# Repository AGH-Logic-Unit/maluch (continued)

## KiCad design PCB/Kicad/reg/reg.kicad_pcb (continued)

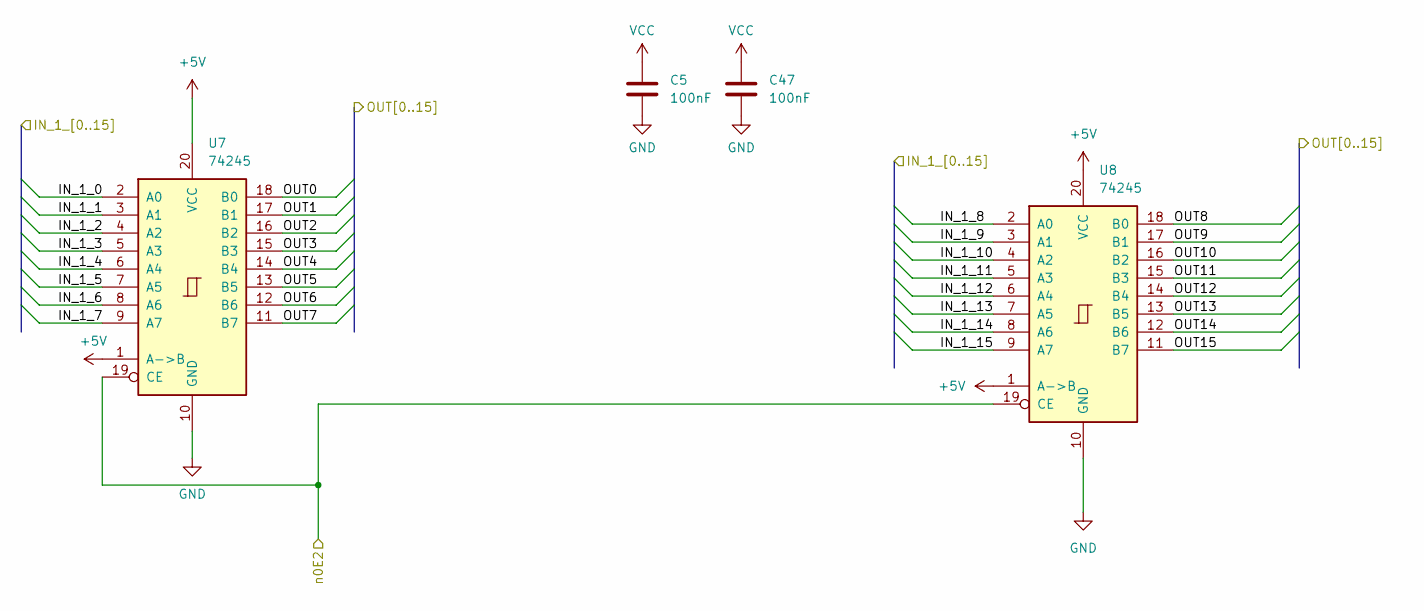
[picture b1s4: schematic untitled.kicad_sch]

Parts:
C5, C47: 100nF; C_0402_1005Metric
U7, U8: 74245; TSSOP-20_4.4x6.5mm_P0.65mm

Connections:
+5V: C5.1, C47.1, U7.1 (A->B), U7.20 (VCC), U8.1 (A->B), U8.20 (VCC); also elsewhere on the board
/16 bit buffor23/OUT0: U7.18 (B0); also elsewhere on the board
/16 bit buffor23/OUT1: U7.17 (B1); also elsewhere on the board
/16 bit buffor23/OUT2: U7.16 (B2); also elsewhere on the board
/16 bit buffor23/OUT3: U7.15 (B3); also elsewhere on the board
/16 bit buffor23/OUT4: U7.14 (B4); also elsewhere on the board
/16 bit buffor23/OUT5: U7.13 (B5); also elsewhere on the board
/16 bit buffor23/OUT6: U7.12 (B6); also elsewhere on the board
/16 bit buffor23/OUT7: U7.11 (B7); also elsewhere on the board
/16 bit buffor23/OUT8: U8.18 (B0); also elsewhere on the board
/16 bit buffor23/OUT9: U8.17 (B1); also elsewhere on the board
/16 bit buffor23/OUT10: U8.16 (B2); also elsewhere on the board
/16 bit buffor23/OUT11: U8.15 (B3); also elsewhere on the board
/16 bit buffor23/OUT12: U8.14 (B4); also elsewhere on the board
/16 bit buffor23/OUT13: U8.13 (B5); also elsewhere on the board
/16 bit buffor23/OUT14: U8.12 (B6); also elsewhere on the board
/16 bit buffor23/OUT15: U8.11 (B7); also elsewhere on the board
/data0: U7.2 (A0); also elsewhere on the board
/data1: U7.3 (A1); also elsewhere on the board
/data2: U7.4 (A2); also elsewhere on the board
/data3: U7.5 (A3); also elsewhere on the board
/data4: U7.6 (A4); also elsewhere on the board
/data5: U7.7 (A5); also elsewhere on the board
/data6: U7.8 (A6); also elsewhere on the board
/data7: U7.9 (A7); also elsewhere on the board
/data8: U8.2 (A0); also elsewhere on the board
/data9: U8.3 (A1); also elsewhere on the board
/data10: U8.4 (A2); also elsewhere on the board
/data11: U8.5 (A3); also elsewhere on the board
/data12: U8.6 (A4); also elsewhere on the board
/data13: U8.7 (A5); also elsewhere on the board
/data14: U8.8 (A6); also elsewhere on the board
/data15: U8.9 (A7); also elsewhere on the board
/r1we: U7.19 (CE), U8.19 (CE); also elsewhere on the board
GND: C5.2, C47.2, U7.10 (GND), U8.10 (GND); also elsewhere on the board

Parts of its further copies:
C6, C11, C12, C48, C49, C50, C51, C52, C53, C54, C55, C56, C57, C58, C59, C60, C61, C62, C63, C64, C65, C66, C67, C68, C69, C70, C71, C72, C73, C74, C75, C76, C77, C78, C79, C80, C81, C82, C83, C84, C87, C88: 100nF; C_0402_1005Metric
U5, U6, U9, U10, U11, U12, U15, U16, U21, U22, U81, U82, U107, U108, U109, U110, U111, U112, U113, U114, U115, U116, U117, U118, U119, U120, U121, U122, U123, U124, U125, U126, U127, U128, U129, U130, U131, U132, U133, U134, U135, U136: 74245; TSSOP-20_4.4x6.5mm_P0.65mm

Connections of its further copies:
+5V: C6.1, C11.1, C12.1, C48.1, C49.1, C50.1, C51.1, C52.1, C53.1, C54.1, C55.1, C56.1, C57.1, C58.1, C59.1, C60.1, C61.1, C62.1, C63.1, C64.1, C65.1, C66.1, C67.1, C68.1, C69.1, C70.1, C71.1, C72.1, C73.1, C74.1, C75.1, C76.1, C77.1, C78.1, C79.1, C80.1, C81.1, C82.1, C83.1, C84.1, C87.1, C88.1, U5.1 (A->B), U5.20 (VCC), U6.1 (A->B), U6.20 (VCC), U9.1 (A->B), U9.20 (VCC), U10.1 (A->B), U10.20 (VCC), U11.1 (A->B), U11.20 (VCC), U12.1 (A->B), U12.20 (VCC), U15.1 (A->B), U15.20 (VCC), U16.1 (A->B), U16.20 (VCC), U21.1 (A->B), U21.20 (VCC), U22.1 (A->B), U22.20 (VCC), U81.1 (A->B), U81.20 (VCC), U82.1 (A->B), U82.20 (VCC), U107.1 (A->B), U107.20 (VCC), U108.1 (A->B), U108.20 (VCC), U109.1 (A->B), U109.20 (VCC), U110.1 (A->B), U110.20 (VCC), U111.1 (A->B), U111.20 (VCC), U112.1 (A->B), U112.20 (VCC), U113.1 (A->B), U113.20 (VCC), U114.1 (A->B), U114.20 (VCC), U115.1 (A->B), U115.20 (VCC), U116.1 (A->B), U116.20 (VCC), U117.1 (A->B), U117.20 (VCC), U118.1 (A->B), U118.20 (VCC), U119.1 (A->B), U119.20 (VCC), U120.1 (A->B), U120.20 (VCC), U121.1 (A->B), U121.20 (VCC), U122.1 (A->B), U122.20 (VCC), U123.1 (A->B), U123.20 (VCC), U124.1 (A->B), U124.20 (VCC), U125.1 (A->B), U125.20 (VCC), U126.1 (A->B), U126.20 (VCC), U127.1 (A->B), U127.20 (VCC), U128.1 (A->B), U128.20 (VCC), U129.1 (A->B), U129.20 (VCC), U130.1 (A->B), U130.20 (VCC), U131.1 (A->B), U131.20 (VCC), U132.1 (A->B), U132.20 (VCC), U133.1 (A->B), U133.20 (VCC), U134.1 (A->B), U134.20 (VCC), U135.1 (A->B), U135.20 (VCC), U136.1 (A->B), U136.20 (VCC); also elsewhere on the board
/16 bit buffor3/n0E2: U5.19 (CE), U6.19 (CE); also elsewhere on the board
/16 bit buffor21/OUT0: U5.18 (B0), U9.18 (B0), U15.2 (A0)
/16 bit buffor21/OUT1: U5.17 (B1), U9.17 (B1), U15.3 (A1)
/16 bit buffor21/OUT2: U5.16 (B2), U9.16 (B2), U15.4 (A2)
/16 bit buffor21/OUT3: U5.15 (B3), U9.15 (B3), U15.5 (A3)
/16 bit buffor21/OUT4: U5.14 (B4), U9.14 (B4), U15.6 (A4)
/16 bit buffor21/OUT5: U5.13 (B5), U9.13 (B5), U15.7 (A5)
/16 bit buffor21/OUT6: U5.12 (B6), U9.12 (B6), U15.8 (A6)
/16 bit buffor21/OUT7: U5.11 (B7), U9.11 (B7), U15.9 (A7)
/16 bit buffor21/OUT8: U6.18 (B0), U10.18 (B0), U16.2 (A0)
/16 bit buffor21/OUT9: U6.17 (B1), U10.17 (B1), U16.3 (A1)
/16 bit buffor21/OUT10: U6.16 (B2), U10.16 (B2), U16.4 (A2)
/16 bit buffor21/OUT11: U6.15 (B3), U10.15 (B3), U16.5 (A3)
/16 bit buffor21/OUT12: U6.14 (B4), U10.14 (B4), U16.6 (A4)
/16 bit buffor21/OUT13: U6.13 (B5), U10.13 (B5), U16.7 (A5)
/16 bit buffor21/OUT14: U6.12 (B6), U10.12 (B6), U16.8 (A6)
/16 bit buffor21/OUT15: U6.11 (B7), U10.11 (B7), U16.9 (A7)
/16 bit buffor23/OUT0: U11.18 (B0); also elsewhere on the board
/16 bit buffor23/OUT1: U11.17 (B1); also elsewhere on the board
/16 bit buffor23/OUT2: U11.16 (B2); also elsewhere on the board
/16 bit buffor23/OUT3: U11.15 (B3); also elsewhere on the board
/16 bit buffor23/OUT4: U11.14 (B4); also elsewhere on the board
/16 bit buffor23/OUT5: U11.13 (B5); also elsewhere on the board
/16 bit buffor23/OUT6: U11.12 (B6); also elsewhere on the board
/16 bit buffor23/OUT7: U11.11 (B7); also elsewhere on the board
/16 bit buffor23/OUT8: U12.18 (B0); also elsewhere on the board
/16 bit buffor23/OUT9: U12.17 (B1); also elsewhere on the board
/16 bit buffor23/OUT10: U12.16 (B2); also elsewhere on the board
/16 bit buffor23/OUT11: U12.15 (B3); also elsewhere on the board
/16 bit buffor23/OUT12: U12.14 (B4); also elsewhere on the board
/16 bit buffor23/OUT13: U12.13 (B5); also elsewhere on the board
/16 bit buffor23/OUT14: U12.12 (B6); also elsewhere on the board
/16 bit buffor23/OUT15: U12.11 (B7); also elsewhere on the board
/16 bit buffor23/n0E2: U11.19 (CE), U12.19 (CE); also elsewhere on the board
/16 bit buffor25/OUT0: U15.18 (B0), U21.18 (B0); also elsewhere on the board
/16 bit buffor25/OUT1: U15.17 (B1), U21.17 (B1); also elsewhere on the board
/16 bit buffor25/OUT2: U15.16 (B2), U21.16 (B2); also elsewhere on the board
/16 bit buffor25/OUT3: U15.15 (B3), U21.15 (B3); also elsewhere on the board
/16 bit buffor25/OUT4: U15.14 (B4), U21.14 (B4); also elsewhere on the board
/16 bit buffor25/OUT5: U15.13 (B5), U21.13 (B5); also elsewhere on the board
/16 bit buffor25/OUT6: U15.12 (B6), U21.12 (B6); also elsewhere on the board
/16 bit buffor25/OUT7: U15.11 (B7), U21.11 (B7); also elsewhere on the board
/16 bit buffor25/OUT8: U16.18 (B0), U22.18 (B0); also elsewhere on the board
/16 bit buffor25/OUT9: U16.17 (B1), U22.17 (B1); also elsewhere on the board
/16 bit buffor25/OUT10: U16.16 (B2), U22.16 (B2); also elsewhere on the board
/16 bit buffor25/OUT11: U16.15 (B3), U22.15 (B3); also elsewhere on the board
/16 bit buffor25/OUT12: U16.14 (B4), U22.14 (B4); also elsewhere on the board
/16 bit buffor25/OUT13: U16.13 (B5), U22.13 (B5); also elsewhere on the board
/16 bit buffor25/OUT14: U16.12 (B6), U22.12 (B6); also elsewhere on the board
/16 bit buffor25/OUT15: U16.11 (B7), U22.11 (B7); also elsewhere on the board
/16 bit buffor26/n0E2: U21.19 (CE), U22.19 (CE); also elsewhere on the board
/16 bit buffor28/IN_1_0: U109.2 (A0); also elsewhere on the board
/16 bit buffor28/IN_1_1: U109.3 (A1); also elsewhere on the board
/16 bit buffor28/IN_1_2: U109.4 (A2); also elsewhere on the board
/16 bit buffor28/IN_1_3: U109.5 (A3); also elsewhere on the board
/16 bit buffor28/IN_1_4: U109.6 (A4); also elsewhere on the board
/16 bit buffor28/IN_1_5: U109.7 (A5); also elsewhere on the board
/16 bit buffor28/IN_1_6: U109.8 (A6); also elsewhere on the board
/16 bit buffor28/IN_1_7: U109.9 (A7); also elsewhere on the board
/16 bit buffor28/IN_1_8: U110.2 (A0); also elsewhere on the board
/16 bit buffor28/IN_1_9: U110.3 (A1); also elsewhere on the board
/16 bit buffor28/IN_1_10: U110.4 (A2); also elsewhere on the board
/16 bit buffor28/IN_1_11: U110.5 (A3); also elsewhere on the board
/16 bit buffor28/IN_1_12: U110.6 (A4); also elsewhere on the board
/16 bit buffor28/IN_1_13: U110.7 (A5); also elsewhere on the board
/16 bit buffor28/IN_1_14: U110.8 (A6); also elsewhere on the board
/16 bit buffor28/IN_1_15: U110.9 (A7); also elsewhere on the board
/16 bit buffor29/IN_1_0: U111.2 (A0); also elsewhere on the board
/16 bit buffor29/IN_1_1: U111.3 (A1); also elsewhere on the board
/16 bit buffor29/IN_1_2: U111.4 (A2); also elsewhere on the board
/16 bit buffor29/IN_1_3: U111.5 (A3); also elsewhere on the board
/16 bit buffor29/IN_1_4: U111.6 (A4); also elsewhere on the board
/16 bit buffor29/IN_1_5: U111.7 (A5); also elsewhere on the board
/16 bit buffor29/IN_1_6: U111.8 (A6); also elsewhere on the board
/16 bit buffor29/IN_1_7: U111.9 (A7); also elsewhere on the board
/16 bit buffor29/IN_1_8: U112.2 (A0); also elsewhere on the board
/16 bit buffor29/IN_1_9: U112.3 (A1); also elsewhere on the board
/16 bit buffor29/IN_1_10: U112.4 (A2); also elsewhere on the board
/16 bit buffor29/IN_1_11: U112.5 (A3); also elsewhere on the board
/16 bit buffor29/IN_1_12: U112.6 (A4); also elsewhere on the board
/16 bit buffor29/IN_1_13: U112.7 (A5); also elsewhere on the board
/16 bit buffor29/IN_1_14: U112.8 (A6); also elsewhere on the board
/16 bit buffor29/IN_1_15: U112.9 (A7); also elsewhere on the board
/16 bit buffor30/IN_1_0: U113.2 (A0); also elsewhere on the board
/16 bit buffor30/IN_1_1: U113.3 (A1); also elsewhere on the board
/16 bit buffor30/IN_1_2: U113.4 (A2); also elsewhere on the board
/16 bit buffor30/IN_1_3: U113.5 (A3); also elsewhere on the board
/16 bit buffor30/IN_1_4: U113.6 (A4); also elsewhere on the board
/16 bit buffor30/IN_1_5: U113.7 (A5); also elsewhere on the board
/16 bit buffor30/IN_1_6: U113.8 (A6); also elsewhere on the board
/16 bit buffor30/IN_1_7: U113.9 (A7); also elsewhere on the board
/16 bit buffor30/IN_1_8: U114.2 (A0); also elsewhere on the board
/16 bit buffor30/IN_1_9: U114.3 (A1); also elsewhere on the board
/16 bit buffor30/IN_1_10: U114.4 (A2); also elsewhere on the board
/16 bit buffor30/IN_1_11: U114.5 (A3); also elsewhere on the board
/16 bit buffor30/IN_1_12: U114.6 (A4); also elsewhere on the board
/16 bit buffor30/IN_1_13: U114.7 (A5); also elsewhere on the board
/16 bit buffor30/IN_1_14: U114.8 (A6); also elsewhere on the board
/16 bit buffor30/IN_1_15: U114.9 (A7); also elsewhere on the board
/16 bit buffor31/IN_1_0: U115.2 (A0); also elsewhere on the board
/16 bit buffor31/IN_1_1: U115.3 (A1); also elsewhere on the board
/16 bit buffor31/IN_1_2: U115.4 (A2); also elsewhere on the board
/16 bit buffor31/IN_1_3: U115.5 (A3); also elsewhere on the board
/16 bit buffor31/IN_1_4: U115.6 (A4); also elsewhere on the board
/16 bit buffor31/IN_1_5: U115.7 (A5); also elsewhere on the board
/16 bit buffor31/IN_1_6: U115.8 (A6); also elsewhere on the board
/16 bit buffor31/IN_1_7: U115.9 (A7); also elsewhere on the board
/16 bit buffor31/IN_1_8: U116.2 (A0); also elsewhere on the board
/16 bit buffor31/IN_1_9: U116.3 (A1); also elsewhere on the board
/16 bit buffor31/IN_1_10: U116.4 (A2); also elsewhere on the board
/16 bit buffor31/IN_1_11: U116.5 (A3); also elsewhere on the board
/16 bit buffor31/IN_1_12: U116.6 (A4); also elsewhere on the board
/16 bit buffor31/IN_1_13: U116.7 (A5); also elsewhere on the board
/16 bit buffor31/IN_1_14: U116.8 (A6); also elsewhere on the board
/16 bit buffor31/IN_1_15: U116.9 (A7); also elsewhere on the board
/16 bit buffor32/IN_1_0: U117.2 (A0); also elsewhere on the board
/16 bit buffor32/IN_1_1: U117.3 (A1); also elsewhere on the board
/16 bit buffor32/IN_1_2: U117.4 (A2); also elsewhere on the board
/16 bit buffor32/IN_1_3: U117.5 (A3); also elsewhere on the board
/16 bit buffor32/IN_1_4: U117.6 (A4); also elsewhere on the board
/16 bit buffor32/IN_1_5: U117.7 (A5); also elsewhere on the board
/16 bit buffor32/IN_1_6: U117.8 (A6); also elsewhere on the board
/16 bit buffor32/IN_1_7: U117.9 (A7); also elsewhere on the board
/16 bit buffor32/IN_1_8: U118.2 (A0); also elsewhere on the board
/16 bit buffor32/IN_1_9: U118.3 (A1); also elsewhere on the board
/16 bit buffor32/IN_1_10: U118.4 (A2); also elsewhere on the board
/16 bit buffor32/IN_1_11: U118.5 (A3); also elsewhere on the board
/16 bit buffor32/IN_1_12: U118.6 (A4); also elsewhere on the board
/16 bit buffor32/IN_1_13: U118.7 (A5); also elsewhere on the board
/16 bit buffor32/IN_1_14: U118.8 (A6); also elsewhere on the board
/16 bit buffor32/IN_1_15: U118.9 (A7); also elsewhere on the board
/16 bit buffor33/IN_1_0: U119.2 (A0); also elsewhere on the board
/16 bit buffor33/IN_1_1: U119.3 (A1); also elsewhere on the board
/16 bit buffor33/IN_1_2: U119.4 (A2); also elsewhere on the board
/16 bit buffor33/IN_1_3: U119.5 (A3); also elsewhere on the board
/16 bit buffor33/IN_1_4: U119.6 (A4); also elsewhere on the board
/16 bit buffor33/IN_1_5: U119.7 (A5); also elsewhere on the board
/16 bit buffor33/IN_1_6: U119.8 (A6); also elsewhere on the board
/16 bit buffor33/IN_1_7: U119.9 (A7); also elsewhere on the board
/16 bit buffor33/IN_1_8: U120.2 (A0); also elsewhere on the board
/16 bit buffor33/IN_1_9: U120.3 (A1); also elsewhere on the board
/16 bit buffor33/IN_1_10: U120.4 (A2); also elsewhere on the board
/16 bit buffor33/IN_1_11: U120.5 (A3); also elsewhere on the board
/16 bit buffor33/IN_1_12: U120.6 (A4); also elsewhere on the board
/16 bit buffor33/IN_1_13: U120.7 (A5); also elsewhere on the board
/16 bit buffor33/IN_1_14: U120.8 (A6); also elsewhere on the board
/16 bit buffor33/IN_1_15: U120.9 (A7); also elsewhere on the board
/16 bit buffor34/IN_1_0: U121.2 (A0); also elsewhere on the board
/16 bit buffor34/IN_1_1: U121.3 (A1); also elsewhere on the board
/16 bit buffor34/IN_1_2: U121.4 (A2); also elsewhere on the board
/16 bit buffor34/IN_1_3: U121.5 (A3); also elsewhere on the board
/16 bit buffor34/IN_1_4: U121.6 (A4); also elsewhere on the board
/16 bit buffor34/IN_1_5: U121.7 (A5); also elsewhere on the board
/16 bit buffor34/IN_1_6: U121.8 (A6); also elsewhere on the board
/16 bit buffor34/IN_1_7: U121.9 (A7); also elsewhere on the board
/16 bit buffor34/IN_1_8: U122.2 (A0); also elsewhere on the board
/16 bit buffor34/IN_1_9: U122.3 (A1); also elsewhere on the board
/16 bit buffor34/IN_1_10: U122.4 (A2); also elsewhere on the board
/16 bit buffor34/IN_1_11: U122.5 (A3); also elsewhere on the board
/16 bit buffor34/IN_1_12: U122.6 (A4); also elsewhere on the board
/16 bit buffor34/IN_1_13: U122.7 (A5); also elsewhere on the board
/16 bit buffor34/IN_1_14: U122.8 (A6); also elsewhere on the board
/16 bit buffor34/IN_1_15: U122.9 (A7); also elsewhere on the board
/16 bit buffor35/IN_1_0: U123.2 (A0); also elsewhere on the board
/16 bit buffor35/IN_1_1: U123.3 (A1); also elsewhere on the board
/16 bit buffor35/IN_1_2: U123.4 (A2); also elsewhere on the board
/16 bit buffor35/IN_1_3: U123.5 (A3); also elsewhere on the board
/16 bit buffor35/IN_1_4: U123.6 (A4); also elsewhere on the board
/16 bit buffor35/IN_1_5: U123.7 (A5); also elsewhere on the board
/16 bit buffor35/IN_1_6: U123.8 (A6); also elsewhere on the board
/16 bit buffor35/IN_1_7: U123.9 (A7); also elsewhere on the board
/16 bit buffor35/IN_1_8: U124.2 (A0); also elsewhere on the board
/16 bit buffor35/IN_1_9: U124.3 (A1); also elsewhere on the board
/16 bit buffor35/IN_1_10: U124.4 (A2); also elsewhere on the board
/16 bit buffor35/IN_1_11: U124.5 (A3); also elsewhere on the board
/16 bit buffor35/IN_1_12: U124.6 (A4); also elsewhere on the board
/16 bit buffor35/IN_1_13: U124.7 (A5); also elsewhere on the board
/16 bit buffor35/IN_1_14: U124.8 (A6); also elsewhere on the board
/16 bit buffor35/IN_1_15: U124.9 (A7); also elsewhere on the board
/16 bit buffor36/IN_1_0: U125.2 (A0); also elsewhere on the board
/16 bit buffor36/IN_1_1: U125.3 (A1); also elsewhere on the board
/16 bit buffor36/IN_1_2: U125.4 (A2); also elsewhere on the board
/16 bit buffor36/IN_1_3: U125.5 (A3); also elsewhere on the board
/16 bit buffor36/IN_1_4: U125.6 (A4); also elsewhere on the board
/16 bit buffor36/IN_1_5: U125.7 (A5); also elsewhere on the board
/16 bit buffor36/IN_1_6: U125.8 (A6); also elsewhere on the board
/16 bit buffor36/IN_1_7: U125.9 (A7); also elsewhere on the board
/16 bit buffor36/IN_1_8: U126.2 (A0); also elsewhere on the board
/16 bit buffor36/IN_1_9: U126.3 (A1); also elsewhere on the board
/16 bit buffor36/IN_1_10: U126.4 (A2); also elsewhere on the board
/16 bit buffor36/IN_1_11: U126.5 (A3); also elsewhere on the board
/16 bit buffor36/IN_1_12: U126.6 (A4); also elsewhere on the board
/16 bit buffor36/IN_1_13: U126.7 (A5); also elsewhere on the board
/16 bit buffor36/IN_1_14: U126.8 (A6); also elsewhere on the board
/16 bit buffor36/IN_1_15: U126.9 (A7); also elsewhere on the board
/16 bit buffor37/IN_1_0: U127.2 (A0); also elsewhere on the board
/16 bit buffor37/IN_1_1: U127.3 (A1); also elsewhere on the board
/16 bit buffor37/IN_1_2: U127.4 (A2); also elsewhere on the board
/16 bit buffor37/IN_1_3: U127.5 (A3); also elsewhere on the board
/16 bit buffor37/IN_1_4: U127.6 (A4); also elsewhere on the board
/16 bit buffor37/IN_1_5: U127.7 (A5); also elsewhere on the board
/16 bit buffor37/IN_1_6: U127.8 (A6); also elsewhere on the board
/16 bit buffor37/IN_1_7: U127.9 (A7); also elsewhere on the board
/16 bit buffor37/IN_1_8: U128.2 (A0); also elsewhere on the board
/16 bit buffor37/IN_1_9: U128.3 (A1); also elsewhere on the board
/16 bit buffor37/IN_1_10: U128.4 (A2); also elsewhere on the board
/16 bit buffor37/IN_1_11: U128.5 (A3); also elsewhere on the board
/16 bit buffor37/IN_1_12: U128.6 (A4); also elsewhere on the board
/16 bit buffor37/IN_1_13: U128.7 (A5); also elsewhere on the board
/16 bit buffor37/IN_1_14: U128.8 (A6); also elsewhere on the board
/16 bit buffor37/IN_1_15: U128.9 (A7); also elsewhere on the board
/16 bit buffor38/IN_1_0: U129.2 (A0); also elsewhere on the board
/16 bit buffor38/IN_1_1: U129.3 (A1); also elsewhere on the board
/16 bit buffor38/IN_1_2: U129.4 (A2); also elsewhere on the board
/16 bit buffor38/IN_1_3: U129.5 (A3); also elsewhere on the board
/16 bit buffor38/IN_1_4: U129.6 (A4); also elsewhere on the board
/16 bit buffor38/IN_1_5: U129.7 (A5); also elsewhere on the board
/16 bit buffor38/IN_1_6: U129.8 (A6); also elsewhere on the board
/16 bit buffor38/IN_1_7: U129.9 (A7); also elsewhere on the board
/16 bit buffor38/IN_1_8: U130.2 (A0); also elsewhere on the board
/16 bit buffor38/IN_1_9: U130.3 (A1); also elsewhere on the board
/16 bit buffor38/IN_1_10: U130.4 (A2); also elsewhere on the board
/16 bit buffor38/IN_1_11: U130.5 (A3); also elsewhere on the board
/16 bit buffor38/IN_1_12: U130.6 (A4); also elsewhere on the board
/16 bit buffor38/IN_1_13: U130.7 (A5); also elsewhere on the board
/16 bit buffor38/IN_1_14: U130.8 (A6); also elsewhere on the board
/16 bit buffor38/IN_1_15: U130.9 (A7); also elsewhere on the board
/16 bit buffor39/IN_1_0: U131.2 (A0); also elsewhere on the board
/16 bit buffor39/IN_1_1: U131.3 (A1); also elsewhere on the board
/16 bit buffor39/IN_1_2: U131.4 (A2); also elsewhere on the board
/16 bit buffor39/IN_1_3: U131.5 (A3); also elsewhere on the board
/16 bit buffor39/IN_1_4: U131.6 (A4); also elsewhere on the board
/16 bit buffor39/IN_1_5: U131.7 (A5); also elsewhere on the board
/16 bit buffor39/IN_1_6: U131.8 (A6); also elsewhere on the board
/16 bit buffor39/IN_1_7: U131.9 (A7); also elsewhere on the board
/16 bit buffor39/IN_1_8: U132.2 (A0); also elsewhere on the board
/16 bit buffor39/IN_1_9: U132.3 (A1); also elsewhere on the board
/16 bit buffor39/IN_1_10: U132.4 (A2); also elsewhere on the board
/16 bit buffor39/IN_1_11: U132.5 (A3); also elsewhere on the board
/16 bit buffor39/IN_1_12: U132.6 (A4); also elsewhere on the board
/16 bit buffor39/IN_1_13: U132.7 (A5); also elsewhere on the board
/16 bit buffor39/IN_1_14: U132.8 (A6); also elsewhere on the board
/16 bit buffor39/IN_1_15: U132.9 (A7); also elsewhere on the board
/16 bit buffor40/IN_1_0: U133.2 (A0); also elsewhere on the board
/16 bit buffor40/IN_1_1: U133.3 (A1); also elsewhere on the board
/16 bit buffor40/IN_1_2: U133.4 (A2); also elsewhere on the board
/16 bit buffor40/IN_1_3: U133.5 (A3); also elsewhere on the board
/16 bit buffor40/IN_1_4: U133.6 (A4); also elsewhere on the board
/16 bit buffor40/IN_1_5: U133.7 (A5); also elsewhere on the board
/16 bit buffor40/IN_1_6: U133.8 (A6); also elsewhere on the board
/16 bit buffor40/IN_1_7: U133.9 (A7); also elsewhere on the board
/16 bit buffor40/IN_1_8: U134.2 (A0); also elsewhere on the board
/16 bit buffor40/IN_1_9: U134.3 (A1); also elsewhere on the board
/16 bit buffor40/IN_1_10: U134.4 (A2); also elsewhere on the board
/16 bit buffor40/IN_1_11: U134.5 (A3); also elsewhere on the board
/16 bit buffor40/IN_1_12: U134.6 (A4); also elsewhere on the board
/16 bit buffor40/IN_1_13: U134.7 (A5); also elsewhere on the board
/16 bit buffor40/IN_1_14: U134.8 (A6); also elsewhere on the board
/16 bit buffor40/IN_1_15: U134.9 (A7); also elsewhere on the board
/16 bit buffor41/IN_1_0: U135.2 (A0); also elsewhere on the board
/16 bit buffor41/IN_1_1: U135.3 (A1); also elsewhere on the board
/16 bit buffor41/IN_1_2: U135.4 (A2); also elsewhere on the board
/16 bit buffor41/IN_1_3: U135.5 (A3); also elsewhere on the board
/16 bit buffor41/IN_1_4: U135.6 (A4); also elsewhere on the board
/16 bit buffor41/IN_1_5: U135.7 (A5); also elsewhere on the board
/16 bit buffor41/IN_1_6: U135.8 (A6); also elsewhere on the board
/16 bit buffor41/IN_1_7: U135.9 (A7); also elsewhere on the board
/16 bit buffor41/IN_1_8: U136.2 (A0); also elsewhere on the board
/16 bit buffor41/IN_1_9: U136.3 (A1); also elsewhere on the board
/16 bit buffor41/IN_1_10: U136.4 (A2); also elsewhere on the board
/16 bit buffor41/IN_1_11: U136.5 (A3); also elsewhere on the board
/16 bit buffor41/IN_1_12: U136.6 (A4); also elsewhere on the board
/16 bit buffor41/IN_1_13: U136.7 (A5); also elsewhere on the board
/16 bit buffor41/IN_1_14: U136.8 (A6); also elsewhere on the board
/16 bit buffor41/IN_1_15: U136.9 (A7); also elsewhere on the board
/OUT_5_0: U81.2 (A0); also elsewhere on the board
/OUT_5_1: U81.3 (A1); also elsewhere on the board
/OUT_5_2: U81.4 (A2); also elsewhere on the board
/OUT_5_3: U81.5 (A3); also elsewhere on the board
/OUT_5_4: U81.6 (A4); also elsewhere on the board
/OUT_5_5: U81.7 (A5); also elsewhere on the board
/OUT_5_6: U81.8 (A6); also elsewhere on the board
/OUT_5_7: U81.9 (A7); also elsewhere on the board
/OUT_5_8: U82.2 (A0); also elsewhere on the board
/OUT_5_9: U82.3 (A1); also elsewhere on the board
/OUT_5_10: U82.4 (A2); also elsewhere on the board
/OUT_5_11: U82.5 (A3); also elsewhere on the board
/OUT_5_12: U82.6 (A4); also elsewhere on the board
/OUT_5_13: U82.7 (A5); also elsewhere on the board
/OUT_5_14: U82.8 (A6); also elsewhere on the board
/OUT_5_15: U82.9 (A7); also elsewhere on the board
/OUT_7_0: U81.19 (CE), U82.19 (CE); also elsewhere on the board
/OUT_7_1: U107.19 (CE), U108.19 (CE); also elsewhere on the board
/OUT_7_2: U109.19 (CE), U110.19 (CE); also elsewhere on the board
/OUT_7_3: U111.19 (CE), U112.19 (CE); also elsewhere on the board
/OUT_7_4: U113.19 (CE), U114.19 (CE); also elsewhere on the board
/OUT_7_5: U115.19 (CE), U116.19 (CE); also elsewhere on the board
/OUT_7_6: U117.19 (CE), U118.19 (CE); also elsewhere on the board
/OUT_7_7: U119.19 (CE), U120.19 (CE); also elsewhere on the board
/OUT_7_8: U121.19 (CE), U122.19 (CE); also elsewhere on the board
/OUT_7_9: U123.19 (CE), U124.19 (CE); also elsewhere on the board
/OUT_7_10: U125.19 (CE), U126.19 (CE); also elsewhere on the board
/OUT_7_11: U127.19 (CE), U128.19 (CE); also elsewhere on the board
/OUT_7_12: U129.19 (CE), U130.19 (CE); also elsewhere on the board
/OUT_7_13: U133.19 (CE), U134.19 (CE); also elsewhere on the board
/OUT_7_14: U131.19 (CE), U132.19 (CE); also elsewhere on the board
/OUT_7_15: U135.19 (CE), U136.19 (CE); also elsewhere on the board
/data0: U9.2 (A0), U81.18 (B0), U107.18 (B0), U109.18 (B0), U111.18 (B0), U113.18 (B0), U115.18 (B0), U117.18 (B0), U119.18 (B0), U121.18 (B0), U123.18 (B0), U125.18 (B0), U127.18 (B0), U129.18 (B0), U131.18 (B0), U133.18 (B0), U135.18 (B0); also elsewhere on the board
/data1: U9.3 (A1), U81.17 (B1), U107.17 (B1), U109.17 (B1), U111.17 (B1), U113.17 (B1), U115.17 (B1), U117.17 (B1), U119.17 (B1), U121.17 (B1), U123.17 (B1), U125.17 (B1), U127.17 (B1), U129.17 (B1), U131.17 (B1), U133.17 (B1), U135.17 (B1); also elsewhere on the board
/data2: U9.4 (A2), U81.16 (B2), U107.16 (B2), U109.16 (B2), U111.16 (B2), U113.16 (B2), U115.16 (B2), U117.16 (B2), U119.16 (B2), U121.16 (B2), U123.16 (B2), U125.16 (B2), U127.16 (B2), U129.16 (B2), U131.16 (B2), U133.16 (B2), U135.16 (B2); also elsewhere on the board
/data3: U9.5 (A3), U81.15 (B3), U107.15 (B3), U109.15 (B3), U111.15 (B3), U113.15 (B3), U115.15 (B3), U117.15 (B3), U119.15 (B3), U121.15 (B3), U123.15 (B3), U125.15 (B3), U127.15 (B3), U129.15 (B3), U131.15 (B3), U133.15 (B3), U135.15 (B3); also elsewhere on the board
/data4: U9.6 (A4), U81.14 (B4), U107.14 (B4), U109.14 (B4), U111.14 (B4), U113.14 (B4), U115.14 (B4), U117.14 (B4), U119.14 (B4), U121.14 (B4), U123.14 (B4), U125.14 (B4), U127.14 (B4), U129.14 (B4), U131.14 (B4), U133.14 (B4), U135.14 (B4); also elsewhere on the board
/data5: U9.7 (A5), U81.13 (B5), U107.13 (B5), U109.13 (B5), U111.13 (B5), U113.13 (B5), U115.13 (B5), U117.13 (B5), U119.13 (B5), U121.13 (B5), U123.13 (B5), U125.13 (B5), U127.13 (B5), U129.13 (B5), U131.13 (B5), U133.13 (B5), U135.13 (B5); also elsewhere on the board
/data6: U9.8 (A6), U81.12 (B6), U107.12 (B6), U109.12 (B6), U111.12 (B6), U113.12 (B6), U115.12 (B6), U117.12 (B6), U119.12 (B6), U121.12 (B6), U123.12 (B6), U125.12 (B6), U127.12 (B6), U129.12 (B6), U131.12 (B6), U133.12 (B6), U135.12 (B6); also elsewhere on the board
/data7: U9.9 (A7), U81.11 (B7), U107.11 (B7), U109.11 (B7), U111.11 (B7), U113.11 (B7), U115.11 (B7), U117.11 (B7), U119.11 (B7), U121.11 (B7), U123.11 (B7), U125.11 (B7), U127.11 (B7), U129.11 (B7), U131.11 (B7), U133.11 (B7), U135.11 (B7); also elsewhere on the board
/data8: U10.2 (A0), U82.18 (B0), U108.18 (B0), U110.18 (B0), U112.18 (B0), U114.18 (B0), U116.18 (B0), U118.18 (B0), U120.18 (B0), U122.18 (B0), U124.18 (B0), U126.18 (B0), U128.18 (B0), U130.18 (B0), U132.18 (B0), U134.18 (B0), U136.18 (B0); also elsewhere on the board
/data9: U10.3 (A1), U82.17 (B1), U108.17 (B1), U110.17 (B1), U112.17 (B1), U114.17 (B1), U116.17 (B1), U118.17 (B1), U120.17 (B1), U122.17 (B1), U124.17 (B1), U126.17 (B1), U128.17 (B1), U130.17 (B1), U132.17 (B1), U134.17 (B1), U136.17 (B1); also elsewhere on the board
/data10: U10.4 (A2), U82.16 (B2), U108.16 (B2), U110.16 (B2), U112.16 (B2), U114.16 (B2), U116.16 (B2), U118.16 (B2), U120.16 (B2), U122.16 (B2), U124.16 (B2), U126.16 (B2), U128.16 (B2), U130.16 (B2), U132.16 (B2), U134.16 (B2), U136.16 (B2); also elsewhere on the board
/data11: U10.5 (A3), U82.15 (B3), U108.15 (B3), U110.15 (B3), U112.15 (B3), U114.15 (B3), U116.15 (B3), U118.15 (B3), U120.15 (B3), U122.15 (B3), U124.15 (B3), U126.15 (B3), U128.15 (B3), U130.15 (B3), U132.15 (B3), U134.15 (B3), U136.15 (B3); also elsewhere on the board
/data12: U10.6 (A4), U82.14 (B4), U108.14 (B4), U110.14 (B4), U112.14 (B4), U114.14 (B4), U116.14 (B4), U118.14 (B4), U120.14 (B4), U122.14 (B4), U124.14 (B4), U126.14 (B4), U128.14 (B4), U130.14 (B4), U132.14 (B4), U134.14 (B4), U136.14 (B4); also elsewhere on the board
/data13: U10.7 (A5), U82.13 (B5), U108.13 (B5), U110.13 (B5), U112.13 (B5), U114.13 (B5), U116.13 (B5), U118.13 (B5), U120.13 (B5), U122.13 (B5), U124.13 (B5), U126.13 (B5), U128.13 (B5), U130.13 (B5), U132.13 (B5), U134.13 (B5), U136.13 (B5); also elsewhere on the board
/data14: U10.8 (A6), U82.12 (B6), U108.12 (B6), U110.12 (B6), U112.12 (B6), U114.12 (B6), U116.12 (B6), U118.12 (B6), U120.12 (B6), U122.12 (B6), U124.12 (B6), U126.12 (B6), U128.12 (B6), U130.12 (B6), U132.12 (B6), U134.12 (B6), U136.12 (B6); also elsewhere on the board
/data15: U10.9 (A7), U82.11 (B7), U108.11 (B7), U110.11 (B7), U112.11 (B7), U114.11 (B7), U116.11 (B7), U118.11 (B7), U120.11 (B7), U122.11 (B7), U124.11 (B7), U126.11 (B7), U128.11 (B7), U130.11 (B7), U132.11 (B7), U134.11 (B7), U136.11 (B7); also elsewhere on the board
/mask_restore: U9.19 (CE), U10.19 (CE); also elsewhere on the board
/mask_save: U15.19 (CE), U16.19 (CE); also elsewhere on the board
/mask_saved0: U5.2 (A0); also elsewhere on the board
/mask_saved1: U5.3 (A1); also elsewhere on the board
/mask_saved2: U5.4 (A2); also elsewhere on the board
/mask_saved3: U5.5 (A3); also elsewhere on the board
/mask_saved4: U5.6 (A4); also elsewhere on the board
/mask_saved5: U5.7 (A5); also elsewhere on the board
/mask_saved6: U5.8 (A6); also elsewhere on the board
/mask_saved7: U5.9 (A7); also elsewhere on the board
/mask_saved8: U6.2 (A0); also elsewhere on the board
/mask_saved9: U6.3 (A1); also elsewhere on the board
/mask_saved10: U6.4 (A2); also elsewhere on the board
/mask_saved11: U6.5 (A3); also elsewhere on the board
/mask_saved12: U6.6 (A4); also elsewhere on the board
/mask_saved13: U6.7 (A5); also elsewhere on the board
/mask_saved14: U6.8 (A6); also elsewhere on the board
/mask_saved15: U6.9 (A7); also elsewhere on the board
/r1_out0: U11.2 (A0), U107.2 (A0); also elsewhere on the board
/r1_out1: U11.3 (A1), U107.3 (A1); also elsewhere on the board
/r1_out2: U11.4 (A2), U107.4 (A2); also elsewhere on the board
/r1_out3: U11.5 (A3), U107.5 (A3); also elsewhere on the board
/r1_out4: U11.6 (A4), U107.6 (A4); also elsewhere on the board
/r1_out5: U11.7 (A5), U107.7 (A5); also elsewhere on the board
/r1_out6: U11.8 (A6), U107.8 (A6); also elsewhere on the board
/r1_out7: U11.9 (A7), U107.9 (A7); also elsewhere on the board
/r1_out8: U12.2 (A0), U108.2 (A0); also elsewhere on the board
/r1_out9: U12.3 (A1), U108.3 (A1); also elsewhere on the board
/r1_out10: U12.4 (A2), U108.4 (A2); also elsewhere on the board
/r1_out11: U12.5 (A3), U108.5 (A3); also elsewhere on the board
/r1_out12: U12.6 (A4), U108.6 (A4); also elsewhere on the board
/r1_out13: U12.7 (A5), U108.7 (A5); also elsewhere on the board
/r1_out14: U12.8 (A6), U108.8 (A6); also elsewhere on the board
/r1_out15: U12.9 (A7), U108.9 (A7); also elsewhere on the board
GND: C6.2, C11.2, C12.2, C48.2, C49.2, C50.2, C51.2, C52.2, C53.2, C54.2, C55.2, C56.2, C57.2, C58.2, C59.2, C60.2, C61.2, C62.2, C63.2, C64.2, C65.2, C66.2, C67.2, C68.2, C69.2, C70.2, C71.2, C72.2, C73.2, C74.2, C75.2, C76.2, C77.2, C78.2, C79.2, C80.2, C81.2, C82.2, C83.2, C84.2, C87.2, C88.2, U5.10 (GND), U6.10 (GND), U9.10 (GND), U10.10 (GND), U11.10 (GND), U12.10 (GND), U15.10 (GND), U16.10 (GND), U21.2 (A0), U21.3 (A1), U21.4 (A2), U21.5 (A3), U21.6 (A4), U21.7 (A5), U21.8 (A6), U21.9 (A7), U21.10 (GND), U22.2 (A0), U22.3 (A1), U22.4 (A2), U22.5 (A3), U22.6 (A4), U22.7 (A5), U22.8 (A6), U22.9 (A7), U22.10 (GND), U81.10 (GND), U82.10 (GND), U107.10 (GND), U108.10 (GND), U109.10 (GND), U110.10 (GND), U111.10 (GND), U112.10 (GND), U113.10 (GND), U114.10 (GND), U115.10 (GND), U116.10 (GND), U117.10 (GND), U118.10 (GND), U119.10 (GND), U120.10 (GND), U121.10 (GND), U122.10 (GND), U123.10 (GND), U124.10 (GND), U125.10 (GND), U126.10 (GND), U127.10 (GND), U128.10 (GND), U129.10 (GND), U130.10 (GND), U131.10 (GND), U132.10 (GND), U133.10 (GND), U134.10 (GND), U135.10 (GND), U136.10 (GND); also elsewhere on the board

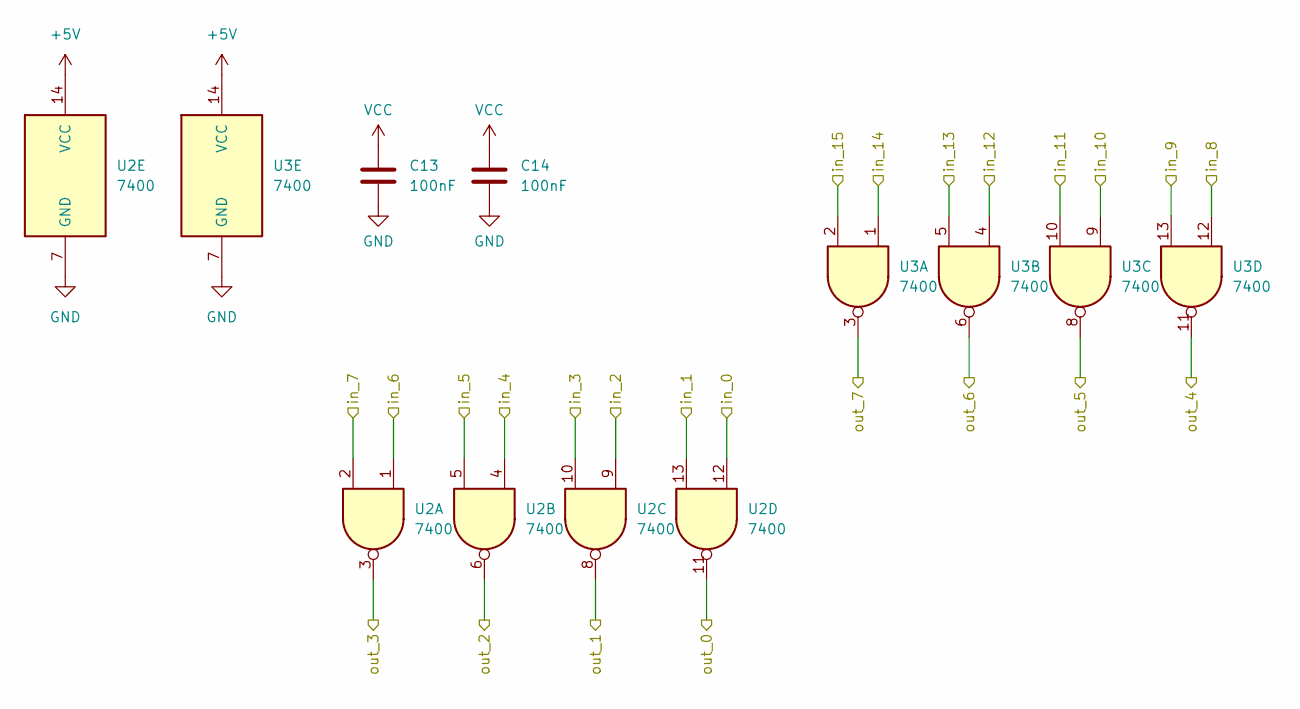
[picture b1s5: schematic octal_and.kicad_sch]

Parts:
C13, C14: 100nF; C_0402_1005Metric
U2, U3: 7400; SO-14_3.9x8.65mm_P1.27mm

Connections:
+5V: C13.1, C14.1, U2.14 (VCC), U3.14 (VCC); also elsewhere on the board
/OUT_5_8: U2.12; also elsewhere on the board
/OUT_5_9: U2.9; also elsewhere on the board
/OUT_5_10: U2.4; also elsewhere on the board
/OUT_5_11: U2.1; also elsewhere on the board
/OUT_5_12: U3.12; also elsewhere on the board
/OUT_5_13: U3.9; also elsewhere on the board
/OUT_5_14: U3.4; also elsewhere on the board
/OUT_5_15: U3.1; also elsewhere on the board
/octal_nand/out_0: U2.11; also elsewhere on the board
/octal_nand/out_1: U2.8; also elsewhere on the board
/octal_nand/out_2: U2.6; also elsewhere on the board
/octal_nand/out_3: U2.3; also elsewhere on the board
/octal_nand/out_4: U3.11; also elsewhere on the board
/octal_nand/out_5: U3.8; also elsewhere on the board
/octal_nand/out_6: U3.6; also elsewhere on the board
/octal_nand/out_7: U3.3; also elsewhere on the board
/r1_out8: U2.13; also elsewhere on the board
/r1_out9: U2.10; also elsewhere on the board
/r1_out10: U2.5; also elsewhere on the board
/r1_out11: U2.2; also elsewhere on the board
/r1_out12: U3.13; also elsewhere on the board
/r1_out13: U3.10; also elsewhere on the board
/r1_out14: U3.5; also elsewhere on the board
/r1_out15: U3.2; also elsewhere on the board
GND: C13.2, C14.2, U2.7 (GND), U3.7 (GND); also elsewhere on the board
